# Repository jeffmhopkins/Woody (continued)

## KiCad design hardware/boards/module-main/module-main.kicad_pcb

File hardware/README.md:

# hardware/ — how this directory is organised

*Schematic sheets are generated from the netlists in KiCad 9, and each
physical board has a directory under [`boards/`](boards/) whose netlist is
assembled from the circuits: [`docs/reference/tooling.md`](../docs/reference/tooling.md) §3.*

One circuit per directory. The directory is the unit: the drawing, the parts,
the declared dependencies and the history of what the circuit *used to be* all
sit together, so a change and its record are never in different places.

```
<board>/<circuit>/<circuit>.md     the schematic: ASCII drawing, derivations,
                                   and an ## Interfaces table of every net
                                   that crosses the circuit's boundary
                  bom.csv          this circuit's parts. A FRAGMENT
                  circuit.yaml     declared dependencies. SEEDED, NOT VERIFIED
                  notes.md         past tense only. No live value belongs here
                  sim/             its SPICE simulation: sims.yaml (what is simulated,
                                   and what each run must show), the decks, and
                                   results.yaml, GENERATED by tools/sim.py run and
                                   held to its inputs by check-staleness. A sim/
                                   with a README and no sims.yaml is a contract not
                                   yet run, and says so
                  <circuit>.kicad_sch  THE SOURCE OF TRUTH where it exists
                                   (ADR 0019): connections and part facts.
                                   Edit in KiCad 9
                  netlist.yaml     EXPORTED from the sheet by tools/kicad.py
                                   where one exists - do not edit. Otherwise
                                   hand-written and authoritative until the
                                   circuit is migrated. Every check reads it

boards/<board>/   one KiCad project per physical board: the root sheet
                  places circuit sheets once per instance; board-netlist.yaml
                  is its exported, flattened netlist

nets.yaml                          at hardware/ root: THE MASTER NET LIST,
                                   which owns every net that crosses a circuit
                                   boundary. A netlist.yaml declares only its
                                   own side; this file owns the net
```

> ### The drawing is not the source of truth. Where a `netlist.yaml` exists, that is.
>
> **An ASCII drawing is a picture.** No tool in this repository can read one,
> so nothing checks that a value in a drawing matches the BOM row for the same
> refdes — and on 2026-09-22 a review found four that did not, including
> `R-FB` drawn at a resistance that is not a purchasable E96 value and an
> entry capacitor drawn at half the BOM's value on the rail that matters.
>
> **`tools/check-netlist.py` checks the drawing against the netlist**, and
> the netlist against `bom.csv` and against `nets.yaml`. It runs `--strict`
> from the commit gate, so a page that gains a drawing and no netlist is a
> failure rather than an entry on a list. It resolves a label against EVERY
> netlist, not only the one beside the page, because several pages draw parts
> they do not own.
>
> **Where a drawing and a row disagree and no netlist covers them, `bom.csv`
> wins.** It is generated from fragments, `merge-bom.py --check` proves the
> master matches them, and the commit hook runs it. A drawing has none of
> that behind it.

| Directory | |
|---|---|
| [`carrier/`](carrier/carrier.md) | The instrument's real-time board — 5 circuits |
| [`cluster/`](cluster/cluster-boards.md) | The four key clusters — two key boards and the main board's two thumb clusters — 3 circuits |
| [`module/`](module/module.md) | The 10HP Eurorack module — 12 circuits |
| [`interfaces/`](interfaces/README.md) | The 3 circuits that cross a board boundary |

## The `Interfaces` table

Every circuit page carries one: every net that crosses that circuit's
boundary, one row each. A PCB netlist is transcribed from these, so a row is
a wiring instruction and two pages disagreeing about a net is a short.

**Two drawing shorthands, and they are shorthands — not missing parts.** The
ASCII drawings use a short spelling where the full refdes would break column
alignment. When transcribing a netlist, expand them:

A netlist declares its own alias with `drawn_as:`, which is what makes the
shorthand checkable rather than merely documented; this table is for the
pages that have no netlist yet.

| Drawn as | BOM row |
|---|---|
| `C-TIMER` | `C-TIMER-LOADSW` |
| `C-GATE` | `C-GATE-LOADSW` |

**`J-UMB` is no longer a shorthand.** It was one, for `J-UMBILICAL`, until
ADR 0017 put a real connector of that name on the main board: `J-UMB` is now
its own row, the header that joins the etherCON's adapter to the main board
(ADR 0021), so "`J-UMB` pin N" on an instrument page is that header, and conductor N of
the umbilical as `umbilical-pinmap` numbers them. Both etherCONs carry it on
contact 9 − N (`hardware/interfaces/spi-link/spi-link.md`). On a module page the umbilical
connector is `J-UMBILICAL`, netlisted as `J-UMB-MOD`; the instrument's
etherCON is `J-UMBILICAL-INST`, netlisted as `J-UMB-INST`. Neither is ever
`J-UMB`.

A cold reviewer filed these two, and `J-UMB` when it was a shorthand, as
refdes that "match nothing in `bom.csv`", which was fair — nothing said
otherwise. They are listed here once rather
than expanded in ~40 drawing sites, because widening a label inside a drawing
shifts every column to its right, and that drift is itself a recorded defect
on these pages. One more, an unlabelled `N-FET`, was **not** a shorthand: it
is `Q-LOADSW`, a row created after that drawing was last touched, and it is
now labelled.

| Column | |
|---|---|
| **Node** | The net's name, **qualified** where the same bare name means different things on different boards. `AGND_SENSE`, `AGND_INST` and `AGND_MOD` are three nets; `AGND` alone is a merge waiting to happen. Each row names the drawing's own spelling so a reader can match the two. |
| **Dir** | This circuit's side of the net: `in`, `out`, `in/out`, `ref` (a return or a reference) or `—` (no connection here — the row is context). |
| **Peer** | A bare `board/circuit` id when the other end is a circuit in this tree, a reference designator or part name when it is not, `—` when there is nothing on the other end. |
| **Figure** | A citation into `config/figures.yaml`. The table names nodes; it **does not restate values.** |

**Exactly one page sources a net.** The page holding the part that drives it
says `out` and "Sourced here"; every other page says `in` and names it. Two
pages both claiming to source one net is the defect this column exists to
make visible — it happened to the DAC's `SCLK`/`DIN`/`SYNC`, in two
byte-identical rows.

The two board-crossing tables (`interfaces/breath-sense-link`,
`interfaces/spi-link`) carry an extra **End** column naming which side of the
cable a node sits on, because for those the board is not implied by the page.

*(This definition sat inline in all 23 circuit pages until 2026-09-21 —
twenty-three copies of one paragraph, in a repository whose first rule is
state it once and cite it. It is here, and they cite it.)*

## `circuit.yaml` and its `depends_on` edges

Every circuit directory carries a `circuit.yaml` whose `depends_on` list is
the dependency graph. Four kinds of edge, and **they are not equally
trustworthy** — this section is the one place that says which:

**`circuit:` edges are VERIFIED.** The rule is mechanical, so any edge can be
checked against the two tables it comes from:

> ONE `circuit:` edge per distinct `board/circuit` id in the **Peer** column of
> this circuit's `## Interfaces` table, AND every such edge is declared from
> **both** ends. A peer that is not a circuit in this tree — a connector, the
> Eurorack bus board, a dev board header — is named in the Peer column by its
> reference designator or its name, and creates no edge.

**`adr:`, `fig:` and `refdes:` edges are SEEDED FROM CO-MENTION and are NOT
VERIFIED.** An edge of those three kinds means *"this page mentions this
thing"*, which is a useful starting graph and a bad finished one. Three were
verified false by a cold reviewer, by reading:

| edge | what it really is |
|---|---|
| `pitch-stage` → `R-BIAS-INAMP` | the page names it as an explicit **contrast** |
| `breath-adc` → `C-STRIP-BULK` | a citation of a note about the LED strip |
| `breath-receive` → `U-OPA-PITCH` | a package-count consequence, not a use |

All three are still declared. **Expect more of that shape.**

**Direction is not recorded.** Several pairs are mutual, which is honest for a
net shared between two circuits and useless for ordering anything.

**What IS guaranteed for every edge, verified or seeded: it RESOLVES.** A
`refdes:` names a BOM row that exists, a `fig:` names a register entry, a
`circuit:` names a declared id. That is what catches a dependency on a deleted
part — the semantic half `CLAUDE.md` §5 says a grep cannot reach.

*(This sat as a 39-line comment header inside all 23 `circuit.yaml` files —
byte-identical, twenty-three copies — until 2026-09-22. Same defect as the
`## Interfaces` definition above, found the same way, fixed the same way.)*

## Two rules that will bite you

**`bom.csv` here is GENERATED.** `tools/merge-bom.py` rebuilds it from the
per-circuit fragments, so **a direct edit survives until the next run of that
tool and then disappears without a word.** Edit the fragment. A row lives with
the circuit **whose page derives its value** — not where it is mentioned, not
where it is mounted. `merge-bom.py --check` proves the master still matches
and `check-staleness.py` reports it as a FAIL, loudly rather than silently —
but the hook only reports; nothing blocks the commit (`CLAUDE.md`, rule 2).

**Numbers shared between documents are not written here.** They live in
`config/figures.yaml`, stated once by their owner and **cited by name**
everywhere else. This whole repository is organised around one recorded
failure — a value changes and the documents derived from it do not follow —
and citation is the only form that cannot go stale. `CLAUDE.md` has the rule
and the three-step procedure for changing a tracked figure.

## What is deliberately not here

`hardware/unplaced.csv` holds the BOM rows **no schematic page derives**.
That is a count, not a dumping ground: a part nobody has drawn.

It has shrunk twice; `wc -l hardware/unplaced.csv` is the count, and a
number written here goes stale the next time a row is placed. Sixteen rows
were drawn all along — the
DAC, the in-amp, the LM317 and its divider, the entry diodes, the four
beads, the bulk capacitors, both load-switch capacitors, the module's level
shifter and the LT5400 — and were sitting in the undrawn pile because
assignment matched on **reference designator** while those parts are drawn
under a local label (`R1`, `C_cm`, `FB2`, `R_G`) or a part number
(`INA828`, `LM317LZ`, `DAC8568`). A count of undrawn parts that includes
every principal IC on a board is not a count of anything.

What remains is genuinely unplaced, and most of it is mechanical — the oak,
the acrylic, the adhesives, the fasteners — plus the parts whose circuit has
no page yet.

Drawings that span more than one circuit were **left whole** rather than
redrawn, and the circuits cite them. `carrier.md`'s §2 figure carries three
circuits in one connected picture; dividing it would mean redrawing it, and a
redraw is not a move.

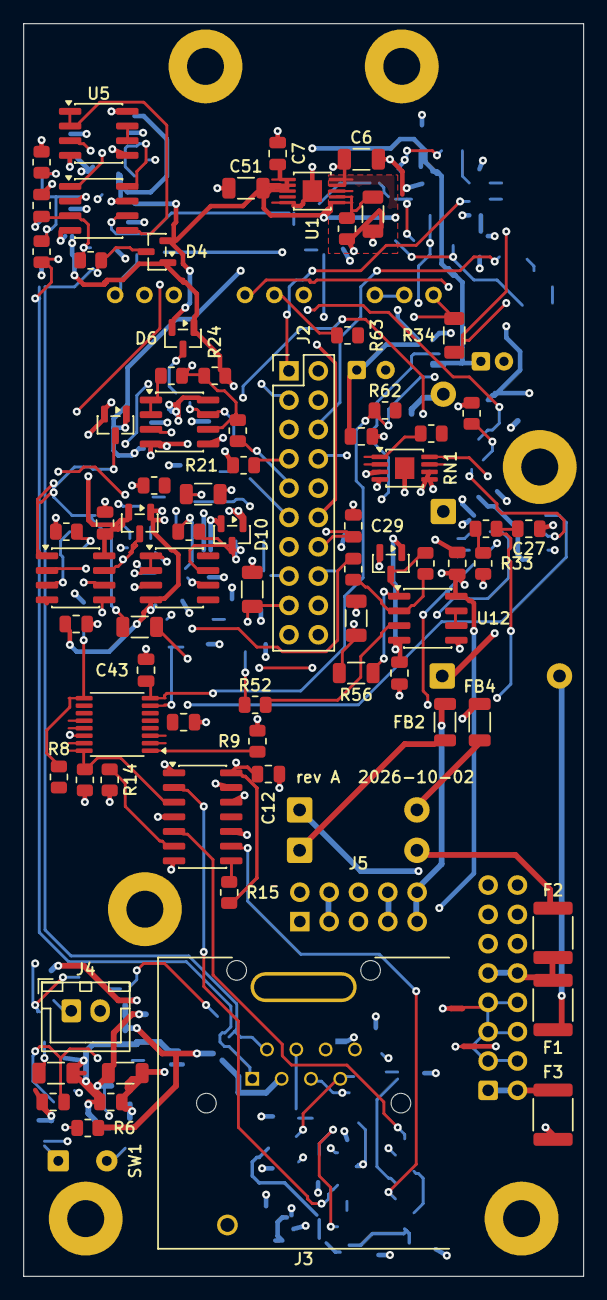
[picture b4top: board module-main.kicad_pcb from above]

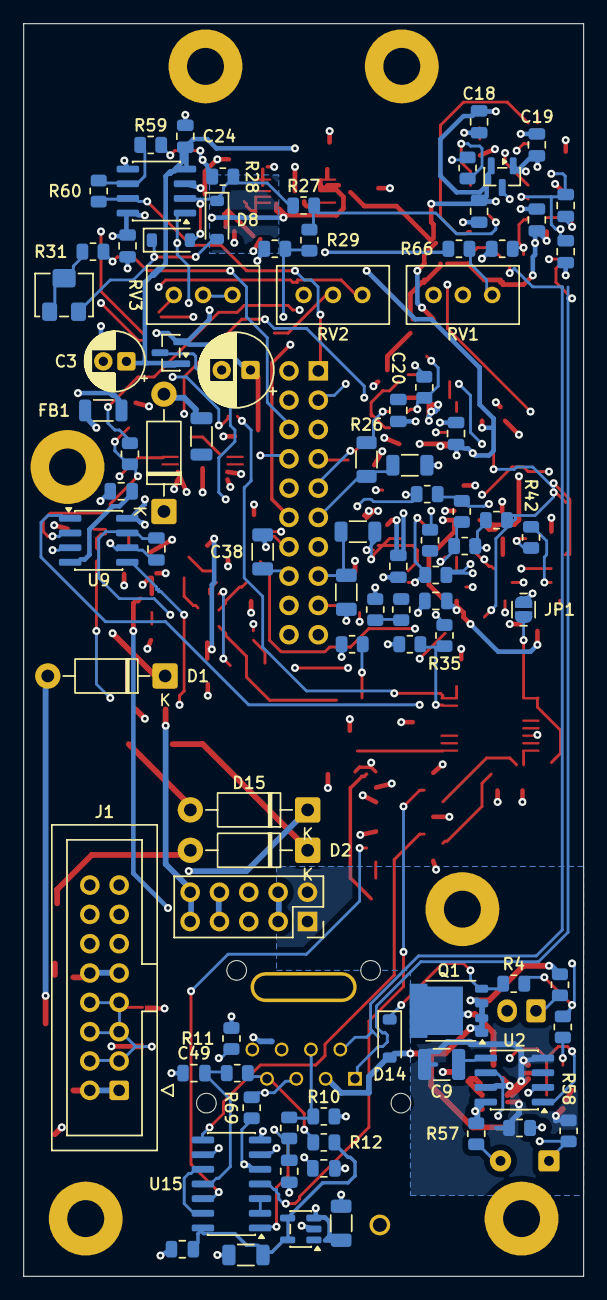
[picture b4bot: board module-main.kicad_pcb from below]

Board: 4 copper layers, 48.5 x 108.5 mm, 173 parts (88 on the bottom side), 110 nets.

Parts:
C1: 100uF; CP_Radial_D6.3mm_P2.50mm
C3: 47uF; CP_Radial_D5.0mm_P2.00mm
C5: 100nF; C_1206_3216Metric
C6, C51: 10uF; C_1206_3216Metric
C7, C10, C11, C12, C16, C17, C18, C19, C20, C21, C23, C24, C25, C26, C30, C31, C32, C33, C34, C35, C40, C43, C50: 100nF; C_0805_2012Metric
C8, C36, C37, C38, C39: 82nF; C_1206_3216Metric
C9: 10uF; C_1210_3225Metric
C13, C14: 1.5nF; C_0805_2012Metric
C15: 15nF; C_0805_2012Metric
C22: 330nF film; C_1206_3216Metric
C27, C29: 10nF; C_0805_2012Metric
C28: 2.2nF; C_0805_2012Metric
C41, C42: 4.7uF; C_1206_3216Metric
C47, C48, C49: 47pF C0G; C_0805_2012Metric
D1, D2, D3, D15: 1N5817; D_DO-41_SOD81_P10.16mm_Horizontal
D4, D5, D6, D9, D10, D11, D12, D13: BAV99; SOT-23
D7, D8: 1N4448W; D_SOD-123
D14: 15V; D_SOD-123
F1, F3: MF-MSMF020/60-2; Fuse_1812_4532Metric
F2: MF-MSMF075/33X-2; Fuse_1812_4532Metric
FB1, FB2, FB3, FB4: 600R @ 100MHz; L_1206_3216Metric
H1: MECH-STANDOFF-MOD 1; MountingHole_3.2mm_M3_Pad
H2: MECH-STANDOFF-MOD 2; MountingHole_3.2mm_M3_Pad
H3: MECH-PANEL-STANDOFF-MOD 1; MountingHole_3.2mm_M3_Pad
H4: MECH-PANEL-STANDOFF-MOD 2; MountingHole_3.2mm_M3_Pad
H5: MECH-STANDOFF-ISO 1; MountingHole_3.2mm_M3_Pad
H6: MECH-STANDOFF-ISO 2; MountingHole_3.2mm_M3_Pad
J1: 2x8 2.54mm shrouded box header (16-pin); IDC-Header_2x08_P2.54mm_Vertical
J2: 2x10 2.54mm pin header; PinHeader_2x10_P2.54mm_Vertical
J3: Neutrik NE8FAV; Neutrik_NE8FAV_etherCON_Vertical
J4: JST B2B-XH-A; JST_XH_B2B-XH-A_1x02_P2.50mm_Vertical
J5: 2x5 2.54mm pin header; PinHeader_2x05_P2.54mm_Vertical
JP1: 2-pad solder link; SolderJumper-2_P1.3mm_Open_RoundedPad1.0x1.5mm
NT1, NT2, NT3: net tie; NetTie-2_SMD_Pad0.5mm
Q1: PSMN2R0-30YLE; LFPAK56
R1: 52.3k 0.1%; R_0805_2012Metric
R3: 50m 1% 1W; R_1206_3216Metric
R4: 10R 5%; R_0805_2012Metric
R5: 1k 5%; R_0805_2012Metric
R6: 35.7k 1%; R_0805_2012Metric
R7: 5.11k 1%; R_0805_2012Metric
R8, R10, R11, R13, R14, R15, R22, R28, R29, R30, R58, R59: 10k 1%; R_0805_2012Metric
R9: 0R strap; R_0805_2012Metric
R12, R33, R36, R38, R43, R48, R53: 100k 1%; R_0805_2012Metric
R16, R17, R39, R44, R49, R54, R65: 10k 0.1%; R_0805_2012Metric
R18, R19: 1M 1%; R_0805_2012Metric
R20: 42.2k 0.1%; R_0805_2012Metric
R21: 7.15k 1%; R_0805_2012Metric
R23: 21.0k 1%; R_0805_2012Metric
R24: 95.3k 1%; R_0805_2012Metric
R25: 40.2k 1%; R_0805_2012Metric
R26, R34, R41, R46, R51, R56: 1k 1%, >=500mW; R_1206_3216Metric
R27, R60: 20k 1%; R_0805_2012Metric
R31: 2.7k 1%; R_0805_2012Metric
R32, R35, R37, R42, R47, R52, R68, R69, R70: 1k 1%; R_0805_2012Metric
R40, R45, R50, R55: 30k 0.1%; R_0805_2012Metric
R57: 68k 1%; R_0805_2012Metric
R61: 100R 0.1%; R_0805_2012Metric
R62: 1k 0.1%; R_0805_2012Metric
R63: 22.1k 0.1%; R_0805_2012Metric
R64: 200R 0.1%; R_0805_2012Metric
R66: 42.2k 1%; R_0805_2012Metric
R71: 2k2 1%; R_0805_2012Metric
RN1: 10k; MSOP-8-1EP_3x3mm_P0.65mm_EP1.68x1.88mm
RV1, RV2: 10k multiturn cermet; Potentiometer_Bourns_3296W_Vertical
RV3: 200R multiturn cermet; Potentiometer_Bourns_3296W_Vertical
RV4: 10k 10% sealed SMD cermet; Potentiometer_Bourns_3224W_Vertical
SW1: NKK M2011SD4G01; SolderWire-0.25sqmm_1x02_P4.2mm_D0.65mm_OD1.7mm
U1: LT3042EMSE; MSOP-10-1EP_3x3mm_P0.5mm_EP1.68x1.88mm
U2: LT1641-1IS8; SOIC-8_3.9x4.9mm_P1.27mm
U3: DAC8568ICPW; TSSOP-16_4.4x5mm_P0.65mm
U4: 74AHCT125; SOIC-14_3.9x8.7mm_P1.27mm
U5, U7, U9, U10, U11, U12: OPA2197; SOIC-8_3.9x4.9mm_P1.27mm
U6: INA828IDR; SOIC-8_3.9x4.9mm_P1.27mm
U8: OPA2197IDR; SOIC-8_3.9x4.9mm_P1.27mm
U13: ADP7118AUJZ-5.0; TSOT-23-5
U15: 74AHCT14; SOIC-14_3.9x8.7mm_P1.27mm

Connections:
/AGND_SENSE: D4.3, J3.2, R16.1
/BREATH_INAMP_OUT: R27.1, R29.1, U6.6
/BREATH_JACK: C22.1, J2.11, R26.2
/BREATH_SENSE: D5.3, J3.1, R17.1
/BREATH_SHAPED: J2.1, R60.2, U8.7
/CS_MOD: J3.7, R12.1, R70.1
/DAC_AVDD: C6.1, C11.1, C12.1, J2.12, R8.1, R15.2, R66.1, U1.9, U1.10, U3.3, U4.14
/DAC_CH1: R32.1, R33.1, U3.4
/DAC_CH2: R37.1, R38.1, U3.13
/DAC_CH3: R42.1, R43.1, U3.5
/DAC_CH4: R47.1, R48.1, U3.12
/DAC_CH5: R52.1, R53.1, U3.6
/DAC_CH7: R35.1, R36.1, U3.7
/DIN: R14.1, U3.15, U4.6
/GAIN_FLOOR: J2.7, R21.1
/GAIN_WIPER: J2.3, U7.3
/ISO_FB2: FB2.2, J5.9, J5.10
/ISO_FILT_NEG: FB4.2, J5.7, J5.8
/MOD1_JACK: C36.1, J2.15, R41.2
/MOD2_JACK: C37.1, J2.17, R46.2
/MOD3_JACK: C38.1, J2.16, R51.2
/MOD4_JACK: C39.1, J2.20, R56.2
/MOSI: J3.5, R11.1, R69.1
/OFFSET_WIPER: J2.9, R23.1
/PITCH_JACK: C29.1, J2.14, R34.2, RV3.1
/RESP_V_IN_HALF: J2.4, R29.2, R30.1
/RESP_V_SHAPED: J2.8, R28.2, R59.1, U8.1
/RESP_WIPER: J2.6, R31.1
/SCLK: J3.4, R10.1, R68.1
/SCLK_DAC: R13.1, U3.16, U4.3
/SYNC: R15.1, U3.2, U4.8
/UMBILICAL_POS12: D14.2, J3.3, Q1.1, Q1.2, Q1.3, R6.1, R71.1
/VREFOUT: C43.1, R62.1, RV2.3, U3.8
/breath-output-stage/BREATH_OUT: D6.3, R25.2, R26.1, U7.7
/breath-output-stage/BUF_OUT: R22.1, U7.1, U7.2
/breath-output-stage/SUM_NODE: R22.2, R23.2, R24.2, R25.1, U7.6
/breath-receive-stage/GAIN_SET: R20.1, U6.1
/breath-receive-stage/GAIN_SET_B: R20.2, U6.8
/breath-receive-stage/IN_NEG: C14.1, C15.2, R17.2, R19.1, U6.2
/breath-receive-stage/IN_POS: C13.1, C15.1, R16.2, R18.1, U6.3
/breath-receive-stage/REF_DRIVE: U5.1, U5.2, U6.5
/breath-receive-stage/SPARE_B_OUT: U5.6, U5.7
/breath-receive-stage/TRIM_WIPER: RV1.2, U5.3
/breath-receive-stage/ZERO_TOP: R66.2, RV1.3
/breath-response-shaper/DIODE_BRANCH: D7.1, D8.2, RV4.3
/breath-response-shaper/RESP_TRIM: R31.2, RV4.1, RV4.2
/breath-response-shaper/RESTORE_SUM: R59.2, R60.1, U8.6
/breath-response-shaper/VIRTUAL_GND: D7.2, D8.1, R27.2, R28.1, U8.2
/dac8568/CLR: JP1.1, R8.2, U3.9
/dac8568/LDAC: R9.1, U3.1
/digital-and-supervision/CS_BUF: U4.9, U15.12
/digital-and-supervision/CS_N: U15.10, U15.13
/digital-and-supervision/CS_RC: C49.1, R70.2, U15.11
/digital-and-supervision/MOSI_BUF: U4.5, U15.8
/digital-and-supervision/MOSI_N: U15.6, U15.9
/digital-and-supervision/MOSI_RC: C48.1, R69.2, U15.5
/digital-and-supervision/SCLK_BUF: U4.2, U15.4
/digital-and-supervision/SCLK_N: U15.2, U15.3
/digital-and-supervision/SCLK_RC: C47.1, R68.2, U15.1
/mod-channels/MINUS_1: R39.2, R40.1, U10.6
/mod-channels/MINUS_2: R44.2, R45.1, U11.2
/mod-channels/MINUS_3: R49.2, R50.1, U11.6
/mod-channels/MINUS_4: R54.2, R55.1, U12.2
/mod-channels/OUT_1: D10.3, R40.2, R41.1, U10.7
/mod-channels/OUT_2: D11.3, R45.2, R46.1, U11.1
/mod-channels/OUT_3: D12.3, R50.2, R51.1, U11.7
/mod-channels/OUT_4: D13.3, R55.2, R56.1, U12.1
/mod-channels/PLUS_1: R37.2, U10.5
/mod-channels/PLUS_2: R42.2, U11.3
/mod-channels/PLUS_3: R47.2, U11.5
/mod-channels/PLUS_4: R52.2, U12.3
/mod-channels/REF_PLUS: R35.2, U10.3
/mod-channels/SPARE_C_OUT: U12.6, U12.7
/mod-channels/VREF_MOD: R39.1, R44.1, R49.1, R54.1, U10.1, U10.2
/panel-led/LED_ANODE: J4.1, R71.2
/pitch-stage/AMP_OUT: C28.1, D9.3, R34.1, U9.7
/pitch-stage/GAIN_TRIM_MID: RN1.7, RV3.2, RV3.3
/pitch-stage/MINUS_NODE: C28.2, RN1.2, RN1.8, U9.6
/pitch-stage/PLUS_NODE: C27.1, R32.2, U9.5
/pitch-stage/R1_BOTTOM: R61.1, RN1.1
/pitch-stage/TRIM_WIPER: R63.1, RV2.2
/pitch-stage/VREF_BUFFERED: R61.2, R64.1, U9.1
/pitch-stage/VREF_FB: R64.2, R65.1, U9.2
/pitch-stage/VREF_SUM: R62.2, R63.2, U9.3
/power-entry/BUS_GND: J1.3, J1.4, J1.5, J1.6, J1.7, J1.8, NT1.2, NT2.2
/power-entry/BUS_NEG12_RAW: D15.1, F3.1, J1.1, J1.2
/power-entry/BUS_POS12_RAW: F1.1, F2.1, J1.9, J1.10
/power-entry/DAC_REG_SET: C5.1, R1.1, U1.7
/power-entry/NEG12_D4: D15.2, FB4.1
/power-entry/NEG12_FB: D3.2, FB3.1
/power-entry/NEG12_PTC3: D3.1, F3.2
/power-entry/POS12_D1: D1.1, FB1.1
/power-entry/POS12_D2: D2.1, FB2.1
/power-entry/POS12_PTC1: D1.2, F1.2
/power-entry/POS12_PTC2: D2.2, F2.2
/umbilical-load-switch/FB: R6.2, R7.1, U2.2
/umbilical-load-switch/GATE_COMP_MID: C8.1, R5.2
/umbilical-load-switch/GATE_DRIVE: R4.1, R5.1, U2.6
/umbilical-load-switch/GATE_NODE: D14.1, Q1.4, R4.2
/umbilical-load-switch/ON: C40.1, R58.1, SW1.1, U2.1
/umbilical-load-switch/ON_SW: R57.2, SW1.2
/umbilical-load-switch/SENSE_NODE: Q1.5, R3.2, U2.7
/umbilical-load-switch/TIMER: C9.1, U2.5
AGND_MOD: C1.2, C3.2, C5.2, C6.2, C7.2, C11.2, C13.2, C14.2, C16.2, C17.2, C18.2, C19.2, C20.2, C21.2, C22.2, C23.2, C24.2, C25.2, C26.2, C27.2, C29.2, C30.2, C31.2, C32.2, C33.2, C34.2, C35.2, C36.2, C37.2, C38.2, C39.2, C43.2, C51.2, J2.2, J2.5, J2.10, J2.13, J2.18, J4.2, JP1.2, NT1.1, R1.2, R9.2, R18.2, R19.2, R21.2, R30.2, R33.2, R36.2, R38.2, R43.2, R48.2, R53.2, R65.2, RN1.3, RN1.4, RN1.5, RN1.6, RN1.9, RV1.1, RV2.1, U1.5, U1.8, U1.11, U3.14, U5.5, U7.5, U8.3, U8.5, U12.5
DIG_GND: C12.2, C41.2, C42.2, C47.2, C48.2, C49.2, C50.2, J3.8, NT2.1, NT3.2, R10.2, R11.2, R13.2, R14.2, U4.1, U4.4, U4.7, U4.10, U4.12, U4.13, U13.2, U15.7
ISO_POS12: C10.1, J5.3, J5.4, R3.1, R57.1, U2.8
LOGIC_5V: C42.1, C50.1, R12.2, U13.4, U13.5, U15.14
MODULE_ANALOG_NEG12: C3.1, C17.1, C19.1, C21.1, C24.1, C26.1, C31.1, C33.1, C35.1, D4.1, D5.1, D6.1, D9.1, D10.1, D11.1, D12.1, D13.1, FB3.2, R24.1, U5.4, U6.4, U7.4, U8.4, U9.4, U10.4, U11.4, U12.4
MODULE_ANALOG_POS12: C1.1, C7.1, C16.1, C18.1, C20.1, C23.1, C25.1, C30.1, C32.1, C34.1, C41.1, C51.1, D4.2, D5.2, D6.2, D9.2, D10.2, D11.2, D12.2, D13.2, FB1.2, U1.1, U1.2, U1.3, U1.6, U5.8, U6.7, U7.8, U8.8, U9.8, U10.8, U11.8, U12.8, U13.1, U13.3
PWR_GND: C8.2, C9.2, C10.2, C40.2, J3.6, J5.1, J5.2, NT3.1, R7.2, R58.2, U2.4

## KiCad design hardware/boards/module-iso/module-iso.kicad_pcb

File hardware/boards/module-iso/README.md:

# Module iso board — `module-iso`

The Eurorack module's third board (ADR 0023 point 2, amended 2026-10-03 by the
owner: *"3 boards for module is correct"*; issue #22): **the instrument's
isolated supply** — `U-ISO` (RECOM RPA20-2412SAW, ADR 0027) and its filter
(`L-ISO-IN`, `L-CM-ISO`, `C-ISO-BULK` `C2`, `C-ISO-IN`, `C-ISO-Y`,
`C-ISO-OUT`) — on a board of its own, parallel to
[`module-main`](../module-main/README.md) and **behind it**.

**Why a board of its own.** On the main board's rear face `U-ISO`'s 25 mm body
put its pins, its 2 mm isolation gap and its `PWR_GND` return pour in the
middle of the DAC's corner, where the DAC meets the mod channels. Twenty
connections stayed unrouted there, and re-placing the corner first left more,
not fewer (`module-main/README.md`). Off the main board, the converter takes
none of its copper.

**Its outline is derived** in the module CAD (`config/module.yaml`
`iso_board`; `mechanical/module/export/iso-board.dxf`): the boards' side edges,
a bottom edge just above the NE8FAV's tails, a notch at its lower right that
`J-PWR-EURO` and its mated socket stand in, and a top edge (`iso_board.y1`)
below the rear trimmers, so each stays adjustable from behind
(`mechanical/module/drc.echo`, *trimmers adjustable from behind*). It stands
off the main board's rear face on two stock spacers used uncut, at opposite corners,
(`MECH-STANDOFF-ISO`): **the gap is the spacer** (*iso board gap*). Its parts
stand on its **rear** face, away from the main board; on the front only
`U-ISO`'s tails and `J-B2B-ISO`'s posts stand in the gap, over main-board
parts no taller than `iso_board.under_h`.

> **Status: laid out and routed by `tools/pcb.py` (`kind: module`), 2026-10-03.**
> Two layers, **a power layout drawn by hand** (2026-10-03, the owner's review of
> the first, autorouted one; *The layout*). `pcb.py check` passes: KiCad's DRC with schematic parity, nothing
> unrouted, every courtyard inside the board, every CAD-placed part where
> `pcb-geometry.echo` puts it, the isolation gap, and `J-B2B-ISO` mating with
> the main board's pin for pin (`check_b2b`). The mask colour is **not
> decided** — green until the owner says (*Open*).

## J-B2B-ISO — the allocation

A 2 × 5 header (`J-B2B-ISO`, Samtec TSW-105-09-G-D) soldered through this
board and the main board: **pin *k* is one conductor on both**, so both
sheets net it the same (`tools/kicad.py check`) and both layouts put it on the
**top face, unmirrored**, pin 1 at the bottom left seen from the panel
(`pcb-geometry.echo`). Its insulator is on the main board's rear face; this
board has only its posts. Each net on two pins, for the converter's current:

| Pins | Net | Side of the barrier |
|---|---|---|
| 1, 2 | `PWR_GND` | output: `U-ISO`'s return, to the load switch and `NT-UMB-MOD` on the main board |
| 3, 4 | `ISO_POS12` | output: the isolated +12 V, to the load switch |
| 5, 6 | — (open) | **the isolation gap**: two pitches between the sides |
| 7, 8 | `ISO_FILT_NEG` | input: the −12 V leg after `FB4` |
| 9, 10 | `ISO_FB2` | input: the +12 V leg after `PTC-ISO`, `D2` and `FB2` |

The output pairs are at the left end, under `U-ISO`'s output row; the input
pairs at the right, toward `L-ISO-IN` and `L-CM-ISO`.

## The layout

`layout.yaml` beside this file records how the first layout was made; the
`.kicad_pcb` is the source now. `U-ISO` and `J-B2B-ISO` are placed by the
module CAD, `U-ISO` turned so its output row (pins 4, 5, 6) runs along the
bottom beside the header and its input pins (1, 2) are at the top.

**It is a power layout, placed and drawn by hand** — the first layout's
autorouted, one-direction-per-layer tracks were the owner's objection
(2026-10-03: *"the strict vertical/horizontal routing is completely
unnecessary"*). The parts follow the current: `J-B2B-ISO`'s input pairs →
`L-ISO-IN` (`L1`) straight above them → `L-CM-ISO` (`L2`, its IN pads down,
OUT pads up) → `C-ISO-BULK` (`C2`) and `U-ISO`'s input pins at the top, with
`C-ISO-IN` (`C44`) on the front between those pins; then `U-ISO`'s output row →
`C-ISO-OUT` (`C45`) → `J-B2B-ISO`'s output pairs. `C-ISO-Y` (`C46`) is on the
front across the barrier beside the 0V pin. `C44` and `C46` are the only
front-face parts.

- **Three pour regions, each on both faces and stitched**: `PWR_GND` under the
  output side (the rear pour stops short of `U-ISO`'s body), `ISO_VIN_NEG`
  over the converter's input side, `ISO_FILT_NEG` under the filter's input.
  They are the returns; no return is a track.
- **The supply nets are straight runs with 45° bends**, 1.2–1.5 mm wide:
  `ISO_POS12` from +Vout through `C45`'s + pad to pair 3-4; `ISO_VIN_POS` from
  `L2`'s OUT_POS over the top to `C2`'s + pad and down to +Vin (and on the front
  through `C44` to `C46`); `ISO_FB2` and `ISO_FILT_POS` from the header through
  `L1` to `L2`. One via per stitch, none in a supply run.
- **The isolation gap** (`layout.yaml` `isolation:`, 2.0 mm, functional, not
  a safety rating): the output region's pours stop 2 mm or more short of the
  input regions' on both faces, across `U-ISO`'s middle and down past the
  header's open pair 5-6; `C46` bridges it by design.
- The two standoff pads on no net (`power-entry.md`, *Grounding*).

## Files

| File | What it is |
|---|---|
| `module-iso.kicad_sch` (+ power-entry's `iso` page) | **Source** (ADR 0019) |
| `board-netlist.yaml` | Exported (`python3 tools/kicad.py export hardware/boards/module-iso`), with KiCad's ERC |
| `*.sch.png` | Renders, recorded in `hardware/SHEETS.csv` |
| `module-iso.kicad_pcb`, `module-iso.kicad_pro` | **Source** since the first layout: edit in KiCad 9; `python3 tools/pcb.py check hardware/boards/module-iso` holds it |
| `layout.yaml` | How the first layout was made |
| `module-iso.pcb-*.png`, `fab/` | Written by `python3 tools/pcb.py render`, recorded in `hardware/SHEETS.csv` |
| `fp-lib-table`, `sym-lib-table` | Register `hardware/lib/` (`U-ISO`'s and `L-CM-ISO`'s footprints) |

## Open, and what decides each

| Item | Decided by |
|---|---|
| The boards' mask colour (green in `layout.yaml` `fab:` until decided) | The owner, before the first order |
| `J-B2B-ISO`'s LCSC part number (the MPN is the TSW family's, as `J-B2B-MOD`) | The module's parts order |
| The spacers' material: `MECH-STANDOFF-ISO` is the same 8 mm metal stock as `MECH-STANDOFF-MOD`, whose metal part is not chosen yet (its row) | The module CAD owner, with `MECH-STANDOFF-MOD` |

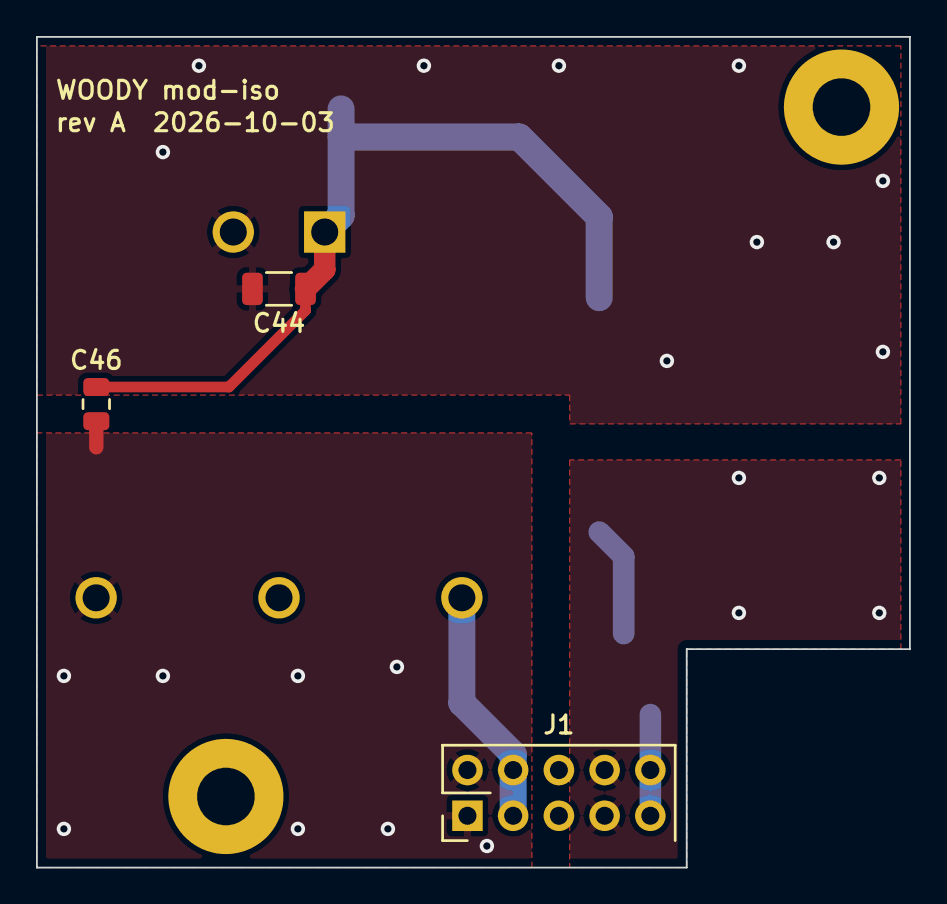
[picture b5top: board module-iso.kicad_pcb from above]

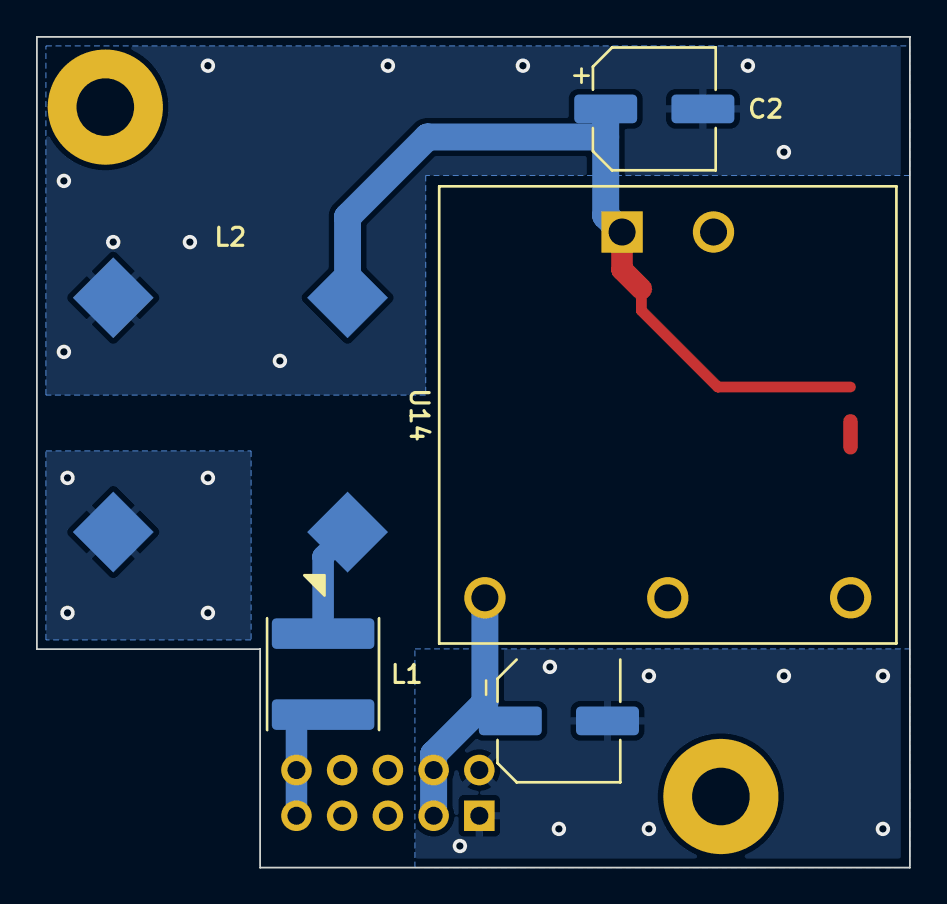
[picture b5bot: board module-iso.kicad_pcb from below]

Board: 2 copper layers, 48.5 x 46.2 mm, 10 parts (5 on the bottom side), 7 nets.

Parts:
C2: 100uF 50V; CP_Elec_6.3x7.7
C44: 4.7uF 50V; C_1206_3216Metric
C45: 100uF 25V; CP_Elec_6.3x5.8
C46: 22nF; C_0805_2012Metric
H1: MECH-STANDOFF-ISO 1; MountingHole_3.2mm_M3_Pad
H2: MECH-STANDOFF-ISO 2; MountingHole_3.2mm_M3_Pad
J1: 2x5 2.54mm pin header; PinHeader_2x05_P2.54mm_Vertical
L1: 22uH; L_Sunlord_SWPA6028S
L2: 1mH; L_CommonModeChoke_Bourns_PM3700
U14: RPA20-2412SAW; Converter_DCDC_RECOM_RPA20-RP20-xxxxSAW_THT

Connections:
/ISO_FB2: J1.9, J1.10, L1.1
/ISO_FILT_NEG: J1.7, J1.8, L2.4
/ISO_POS12: C45.1, J1.3, J1.4, U14.6
/PWR_GND: C45.2, C46.2, J1.1, J1.2, U14.4
/power-entry/ISO_FILT_POS: L1.2, L2.1
/power-entry/ISO_VIN_NEG: C2.2, C44.2, L2.3, U14.2
/power-entry/ISO_VIN_POS: C2.1, C44.1, C46.1, L2.2, U14.1

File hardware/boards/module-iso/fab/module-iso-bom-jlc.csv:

Comment,Designator,Footprint,JLCPCB Part #
100uF 25V,C45,CP_Elec_6.3x5.8,C729678
1mH,L2,L_CommonModeChoke_Bourns_PM3700,C2662215
22nF,C46,C_0805_2012Metric,C77069
22uH,L1,L_Sunlord_SWPA6028S,C51349
4.7uF 50V,C44,C_1206_3216Metric,C132170

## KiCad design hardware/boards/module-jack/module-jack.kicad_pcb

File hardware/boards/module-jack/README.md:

# Module jack board — `module-jack`

The Eurorack module's front board (ADR 0023), behind the panel where the
jacks' bodies put it: the six jacks and the three pots, and nothing else.

**Its outline is a plain rectangle** (ADR 0024 point 15, the owner,
2026-10-01): full width, from just below the bottom jack row's footprints
(`config/module.yaml` `boards.jack_y0`, derived there) to the top edge it
shares with the main board — `mechanical/module/export/jack-board.dxf`. The
toggle's row and the etherCON are below it, so nothing passes through it;
until 2026-10-01 it was a U whose legs reached down beside them.
Everything it connects to is on [`module-main`](../module-main/README.md),
through `J-B2B-MOD`.

> **Status: laid out and routed by `tools/pcb.py` (`kind: module`), 2026-10-02.**
> `pcb.py check` passes: KiCad's DRC with schematic parity is clean, nothing is
> unrouted, every courtyard is inside the board, every CAD-placed part is
> where `mechanical/module/export/pcb-geometry.echo` puts it, and `J-B2B-MOD`
> mates with the main board's pin for pin. Two layers, `AGND_MOD` poured on
> both; layer 1 runs vertically and layer 2 across (`layout.yaml`
> `directions:`). The mask colour is **not decided** — green until the owner
> says (*Open*). The sheets are the source and pass KiCad's ERC. Every part
> has a footprint; the parts still missing a bought part are under *Open*.

## The layout

`layout.yaml` beside this file records how the first layout was made; the
`.kicad_pcb` is the source now. Everything but one part is placed by the
module CAD: the six jacks by their pins along the CAD's pin line, the pots by
their pins, `J-B2B-MOD` on the top face unmirrored, `H1`/`H2` on the CAD's
standoffs. What the layout decided:

- **`D-ESD-PITCH` (`D2`) on the rear, between `J-CV-PITCH`'s tip and its
  switch pad** — pitch-stage.md's *at the jack's tip and sleeve pads, before
  the trace leaves*.
- **`J-B2B-MOD`'s courtyard is drawn on the rear** (`connectors:` `body:
  rear`): its insulator is on the main board's side, so on the front only its
  pins stand between the jacks. On the front it overlapped every jack's
  courtyard.
- **The R0904N's courtyard** (`hardware/lib/woody.pretty`) was its bounding
  box, which reached the standoffs' heads between the pots; it now follows
  the body and the snap-in slots' pads, each 0.25 round.
- The CAD's jack positions put the bottom row's courtyards 0.055 mm inside
  the board's bottom edge (`config/module.yaml` `boards.jack_y0`'s
  derivation), and the outer pots' snap-in lugs 0.4 mm inside the sides.

It places:
- the `jack` pages of [`pitch-stage`](../../module/pitch-stage/pitch-stage.md)
  (`J-CV-PITCH`), [`breath-output-stage`](../../module/breath-output-stage/breath-output-stage.md)
  (`J-CV-BREATH`, `POT-GAIN`, `POT-OFFSET`),
  [`breath-response-shaper`](../../module/breath-response-shaper/breath-response-shaper.md)
  (`POT-RESP`) and [`mod-channels`](../../module/mod-channels/mod-channels.md)
  (`J-CV-MOD1`…`4`);
- **`J-B2B-MOD`** on its root sheet: the same header as the main board's, pin
  for pin. The allocation and its reasoning are in
  [`module-main/README.md`](../module-main/README.md#j-b2b-mod--the-allocation);
  `tools/kicad.py check` fails if the two sheets net a pin differently. This
  instance is `Assembly = none`: the one header is bought once.
  **Lay it out on the TOP side (F.Cu), NOT mirrored**, although its body is
  on this board's rear (the insulator is on the main board's front face).
  Pin *k* is one straight conductor through both boards, so it sits at the
  same panel-frame place on both, and both boards' KiCad top views are the
  panel view (`config/module.yaml` frame note): this board takes the same
  unmirrored pin map as the main board, pin 1 at the top left
  (`mechanical/module/export/pcb-geometry.echo` `J-B2B-MOD`). Put on B.Cu,
  the natural side for a part whose body is on the rear, it mirrors: odd and
  even columns swap and every net lands one column over. `tools/pcb.py
  check` catches that since 2026-10-02 (`pcb_module.check_b2b`): the header
  must be on the top face, and each pin k at the same panel-frame place and
  on the same net as the main board's.

The parts carry the references KiCad gives them on this board (`J1`, `RV2`);
`board-netlist.yaml` gives each one's BOM row (`of`) and circuit (`sheet`).
The same header is `J7` here and `J2` on the main board.

## Files

| File | What it is |
|---|---|
| `module-jack.kicad_sch` (+ the pages it places) | **Source** (ADR 0019) |
| `board-netlist.yaml` | Exported (`python3 tools/kicad.py export hardware/boards/module-jack`), with KiCad's ERC |
| `*.sch.png` | Renders, recorded in `hardware/SHEETS.csv` |
| `module-jack.kicad_pcb`, `module-jack.kicad_pro` | **Source** since the first layout (`python3 tools/pcb.py layout`, then `route`): edit in KiCad 9; `python3 tools/pcb.py check hardware/boards/module-jack` holds it |
| `layout.yaml` | How the first layout was made: the parts' places, the rules, planes and checks' inputs |
| `module-jack.pcb-*.png`, `fab/` | Written by `python3 tools/pcb.py render`, recorded in `hardware/SHEETS.csv` |
| `fp-lib-table`, `sym-lib-table` | Register `hardware/lib/` (the R0904N pot footprint) |

**The standoff pads are on the sheet:** `H1` and `H2` (`MountingHole_3.2mm_M3_Pad`, Row `MECH-STANDOFF-MOD`, excluded from the BOM) on `AGND_MOD` — the two standoffs above the pots (`standoff.at`), which with the six jack nuts are all that hold this board. It has no low standoffs: the main board's two low mounting points go to the panel (`MECH-PANEL-STANDOFF-MOD`, ADR 0024 point 15). The main board's pads are on no net, so they need no symbol and are placed board-only by the layout.

**The power LED is not on this board** since 2026-10-01: `LED-PANEL` is a panel-mount indicator whose lead plugs into `J-LED-PANEL` on the main board's front face (ADR 0024 points 15 and 16), and `J-B2B-MOD` pin 19, which carried its supply, is spare and unconnected here.

## Decided 2026-09-30

- **Two layers, 1.6 mm.** This board's only ground is `AGND_MOD`, arriving on
  `J-B2B-MOD`'s five ground pins (`dig-gnd-topology`).
- **The metal standoffs' pads are `AGND_MOD` here** and on no net on the main
  board, so they add no second tie between the boards.

## Open, and what decides each

| Item | Decided by |
|---|---|
| The pots and jacks have no LCSC number (Thonk and Song Huei/Alpha, bought by hand) | Nothing to decide: hand-placed, bought from the maker's stockists. `POT-GAIN`/`POT-OFFSET` are Song Huei R0904N with the 18-tooth **KC** shaft the T18 knob needs, `POT-RESP` Alpha's centre-click RV09 (rows) |
| The boards' mask colour (green in `layout.yaml` `fab:` until decided) | The owner, before the first order |
| The pots' shaft against the panel hole: the footprint (from drawing R09N-003, `R0904N.pdf` p.2) puts the snap-in slots, and so the shaft, 7.0 mm from the pin row; the module CAD (`config/module.yaml` `pot.pins`, from the STEP) 6.7. The layout places the pins where the CAD does, so the shaft sits 0.3 mm above the CAD's hole centre, inside the hole's 0.5 mm radial play (`pot.hole_d`) | Reading both banked sources again; the first panel's test-fit (`pot.hole_d`'s own `decided_by`) |
| The pots' rotation sense (which end is clockwise). Checked 2026-09-30 against both banked drawings — `R0904N.pdf` p.2 and `RV09AF-40.pdf` p.3 draw pins 1-2-3 with the shaft at full CCW and say nothing about which end the wiper approaches, so the sheets' "CW toward pin 3" stays `[from memory]` | Goods-in, E10: turn each pot fully CCW and read pin 1 to 2 with an ohmmeter — near 0 Ω confirms the sheets; near the full track means swap `CW`/`CCW` on all three symbols before the legends are drawn |
| Whether the reasons for `J-B2B-MOD`'s allocation still hold once the board is laid out. The panel layout is settled (ADR 0024 points 11–13), and the reasons were re-read against it | The layout, against `mechanical/module/export/pcb-geometry.echo` |

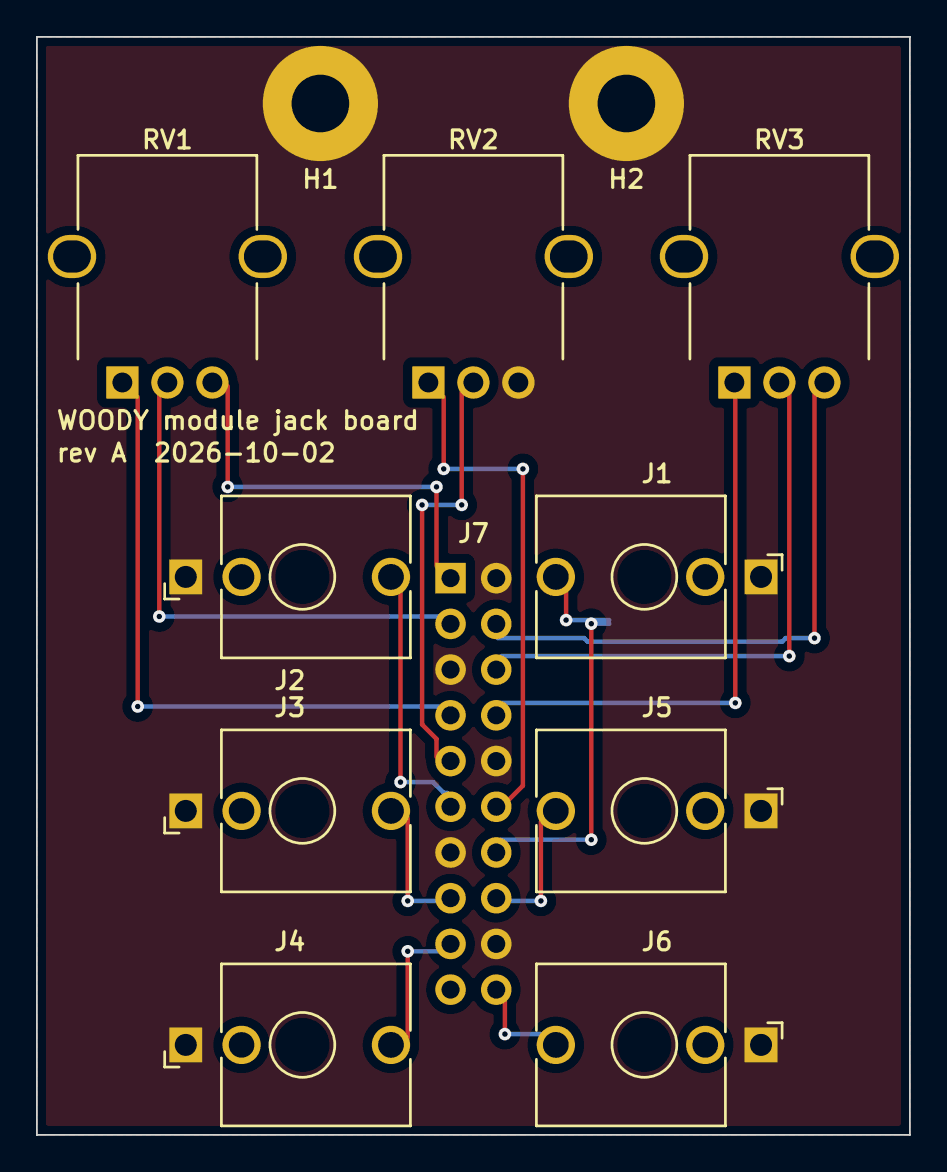
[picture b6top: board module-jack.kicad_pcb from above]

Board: 2 copper layers, 48.5 x 61.0 mm, 13 parts (1 on the bottom side), 15 nets.

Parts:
D2: PESD15VL1BA; D_SOD-323
H1, H2: M3 female-female hex spacer; MountingHole_3.2mm_M3_Pad
J1, J2, J3, J4, J5, J6: PJ398SM; Jack_3.5mm_QingPu_WQP-PJ398SM_Vertical_CircularHoles
J7: 2x10 2.54mm pin header; PinHeader_2x10_P2.54mm_Vertical
RV1, RV3: 50k linear; Potentiometer_SongHuei_R0904N_Single_Vertical
RV2: 10k linear; Potentiometer_SongHuei_R0904N_Single_Vertical

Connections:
/AGND_MOD: D2.2, H1.1, H2.1, J1.S, J2.S, J3.S, J4.S, J5.S, J6.S, J7.2, J7.5, J7.10, J7.13, J7.18, RV2.3
/BREATH_JACK: J2.T, J7.11
/BREATH_SHAPED: J7.1, RV1.3
/DAC_AVDD: J7.12, RV2.1
/GAIN_FLOOR: J7.7, RV1.1
/GAIN_WIPER: J7.3, RV1.2
/MOD1_JACK: J3.T, J7.15
/MOD2_JACK: J4.T, J7.17
/MOD3_JACK: J5.T, J7.16
/MOD4_JACK: J6.T, J7.20
/OFFSET_WIPER: J7.9, RV2.2
/PITCH_JACK: D2.1, J1.T, J7.14
/RESP_V_IN_HALF: J7.4, RV3.3
/RESP_V_SHAPED: J7.8, RV3.1
/RESP_WIPER: J7.6, RV3.2

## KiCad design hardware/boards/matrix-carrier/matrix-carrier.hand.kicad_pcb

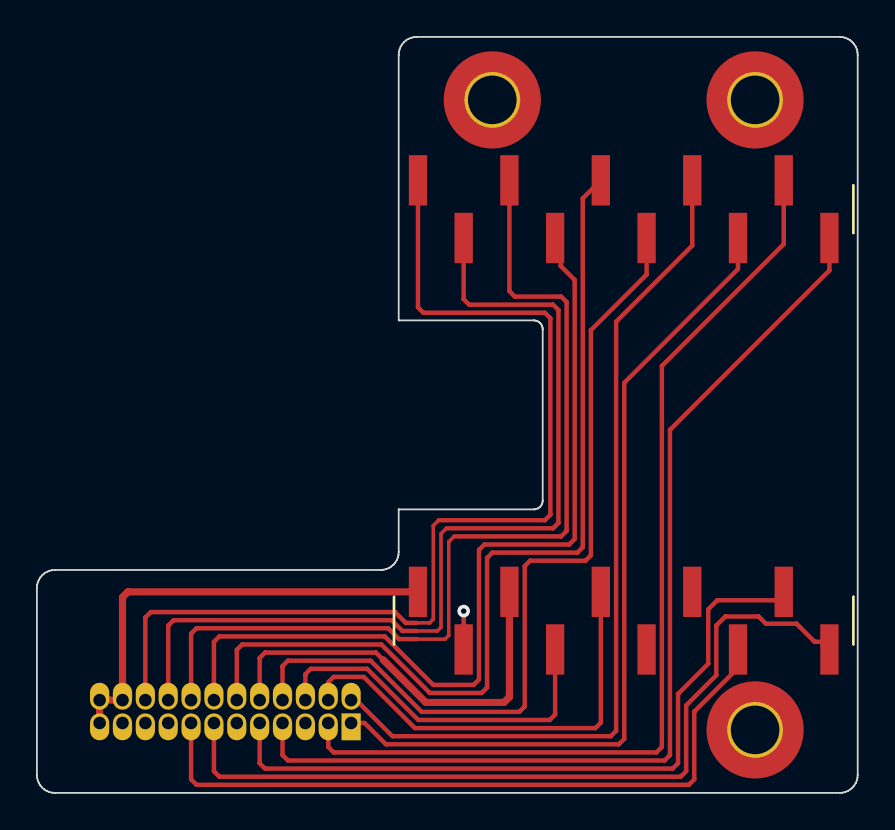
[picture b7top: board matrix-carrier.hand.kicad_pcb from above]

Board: 2 copper layers, 45.6 x 42.0 mm, 6 parts (1 on the bottom side), 18 nets.

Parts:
H1, H2, H3: mount hang; MountingHole_2.7mm_M2.5_Pad_TopBottom
J1: 2x12 1.27mm shrouded box header; IDC-Header_2x12_P1.27mm_XKB_X1270WR_Horizontal
J2, J3: 1x10 2.54mm pin header, SMD; PinHeader_1x10_P2.54mm_Vertical_SMD_Hanxia_PZ2.54-TP-YQ

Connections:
/DEV_3V3: J1.10, J2.3
/INST_5V_A: J1.22, J1.23, J1.24, J2.1
/IO1: J1.13, J2.10
/IO2: J1.9, J2.9
/IO3: J1.15, J2.8
/IO6: J1.4, J2.5
/IO7: J1.6, J2.4
/IO33: J1.20, J3.1
/IO34: J1.18, J3.2
/IO35: J1.16, J3.3
/IO36: J1.14, J3.4
/IO37: J1.12, J3.5
/IO38: J1.8, J3.6
/IO39: J1.2, J3.7
/IO40: J1.1, J3.8
/U0RXD: J1.7, J3.10
/U0TXD: J1.3, J3.9
PWR_GND: H1.1, H2.1, H3.1, J1.5, J1.11, J1.17, J1.21, J2.2

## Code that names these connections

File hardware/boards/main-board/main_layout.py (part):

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     then VS. The buffer stands under the sensor's near edge turned so RAW drops into its
     mouth-side column and VS leaves its tail-side column: the two run down under the
     sensor side by side with AGND between them. They used to cross there.
   - the reference buffer's feedback stands under and beside the pins it serves; REF_5V
     comes in along one line from the reference, tailward of the buffer, passing between
     R-ISO-REF's pads and R-FB-REF's so that it reaches its pin inside VS without a via.
   - the reference's input parts hang from REF_VIN's bus beyond the reference, the 12 V
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    "U1": (277.0, 16.85, ("1", "NE")),
    "R1": (280.3, SPI_Y, ("SCLK", "N")), "R2": (283.3, SPI_Y, ("MOSI", "N")), "R3": (286.3, SPI_Y, ("CS_MOD", "N")),
    "R40": (289.0, SPI_Y - 0.55, ("IO34", "S")),
    "R46": (284.913, 15.6, ("TXD_HDR", "W")),      # its header-side pad over J-UART pin 1
    # RXD's series resistor beside the header, its header pad toward pin 2 (pre-fab review S3)
    "R56": (289.1, 15.95, ("RXD_HDR", "W")),
    # the ADC branch's two series resistors (pre-fab review S1), on top over the long lanes a
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ADC_ROW = 17.5               # the ADC's row: divider, anti-alias, decoupling, bulk, supply resistor
REF_LINE = 20.5               # REF_5V's line from the reference to the buffer; the feedback parts stand on it
PLACE.update({
    # the buffer under the sensor's near edge, turned so SENSOR_RAW drops into pin 5 on the mouth
    # side and VS leaves on the tail side: the two no longer cross under the sensor
    "U3": (14.0, 25.5, ("5", "NW")),
    "C203": (8.9, 26.455, ("SENSOR_RAW", "N")), "C204": (8.9, 22.0, ("INST_POS12", "N")),
    # the reference buffer's feedback: C9 and R9 under the pins they serve, R7 and R8 in the
    # corridor VS climbs; REF_5V passes between R7's pads and between R8's to reach pin 3 inside VS
    "C9": (13.5, REF_LINE, ("REF_MINUS", "N")), "R9": (16.5, REF_LINE, ("BUF_OUT", "N")),
    "R7": (20.6, REF_LINE, ("VS", "N")), "R8": (19.55, 24.865, ("VS", "E")),
    # the reference, tailward on the same line: its output capacitors on the line, its input
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LED_CAP_DX = -6.5             # each LED's 100 nF: this far from its LED's centre, in the row, a millimetre between courtyards
KEEP_CAP = ("C38", "C26")     # the mouth-end LED's stands north of it, off the sensor; the first LED's is beyond the surge diode
PLACE["C11"] = (237.0, 12.5, ("BUCK_IN", "N"))   # its input pad level with the inductor and the regulator
PLACE["C43"] = (219.545, 18.5, ("BUCK_A_OUT", "E"))   # its output pad over the regulator's output pin
PLACE["C38"] = (26.85, 33.0, ("INST_POS12", "W"))

# Every part not named above keeps the place the reviewed board gave it.
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    A = "AGND_INST"
    # the sensor's output: down the mouth edge clear of the sensor's unused pads, through its
    # capacitor's pad, into the buffer's + input
    T("SENSOR_RAW", ["U10.4", (10.34, 45.9), (9.2, 44.76), (9.2, 27.405), "U3.5"])      # down into its capacitor's pad, and level out of it into the pin
    # the buffer's output: one trunk under its own body, pins 6 and 7 a stub each. North it
    # leaves between pins 5 and 4 for the breath pair's via; south between pins 8 and 1, round
    # the mouth side of the feedback capacitor, into the ADC's divider
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    T("ADC_VDD", ["R47.2", (42.888, 16.32), (42.518, 15.95), (30.0, 15.95)], PWR)
    T("ADC_VDD", [(37.47, 15.95), "C2.1"], PWR)
    T("ADC_VDD", [(32.03, 15.95), "C42.1"], PWR)
    T("ADC_VDD", ["C3.1", (30.0, 14.155)], PWR)       # the decoupler straight onto the supply pin, the bus teeing into it
    # 12 V for the buffer, its capacitor at the pin; and for the reference's input resistor
    T("INST_POS12", ["U3.8", (10.07, 23.595), (9.415, 24.25), (8.85, 24.25)], PWR)      # pin, via, capacitor: straight out of the pin, one step up, level into the via
    VIAS.append(("INST_POS12", 8.85, 24.25))
    T("INST_POS12", [(8.85, 24.25), (8.85, 22.95)], PWR)
    T("INST_POS12", ["R6.1", (48.25, 21.35), (47.5, 20.6)], PWR)      # straight out of the pad, one 45 into the via
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    the header on the bottom face to the LED driver. 3V3 is J-MCU pin 15 round the tail end (drawn in
    stage 3); its trunk starts by R49 and runs the bottom face toward the mouth."""
    # 12 V entry and the inrush switch
    T("UMBILICAL_POS12", ["J6.3", (294.64, 31.35), (276.35, 31.35)], 0.8)      # one 45 out of the pin, then one straight line into the surge diode's pad, north of the first LED   # to the surge diode, north of the first LED
    T("UMBILICAL_POS12", ["J6.3", (297.1, 32.31), (298.85, 30.56), "R41.1"], 0.6)   # level out of the pin, one 45, and straight down into R41's pad
    T("UMBILICAL_POS12", ["Q1.2", "C39.1", "R41.1"], 0.5)
    T("INRUSH_GATE", ["Q1.1", "C39.2", "R41.2", "R42.1"])
    T("INRUSH_GATE", ["Q1.1", "C40.1"])
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    T("BUCK_A_OUT", ["U5.3", "C43.1", "Q2.2"], 0.5)
    T("BUCK_A_OUT", [(229.8, 18.5), "C207.2"])
    T("BUCK_A_OUT", [(232.163, 18.5), "U13.3"])
    T("BUCK_A_OUT", ["U13.3", (233.125, 19.45), (233.3, 19.625), (233.3, 21.175), (233.475, 21.35), "U13.6"])      # between the pin rows: all the room there is for the two turns
    T("USBOR_GATE", ["U13.5", "Q2.1"])
    T("USBOR_VCAP", ["C207.1", "U13.1"])
    for pad, x, y in (("U13.2", 231.0, 20.4), ("C208.2", 241.35, 20.6), ("C43.2", 218.07, 16.9)):
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    # the module's SPI, from its resistors to J-UMB: SCLK comes down the tail side of the first LED
    T("SCLK", ["J6.4", (290.07, 29.77), (281.7, 21.4), (280.3, 21.4)])      # into its pad level, as near the centre as MOSI's pad lets the diagonal stand
    T("MOSI", ["J6.5", (288.3, 27.23), (283.3, 22.23), "R2.2"])
    T("CS_MOD", ["J6.7", (294.563, 21.113), "R3.2"])      # one 45 from the pin's centre, then level into the pad
    # the breath pair's last step to J-UMB
    T("BREATH_SENSE", ["J6.1", "R38.2"])
    T("BREATH_SENSE", [(293.25, 37.39), "D5.1"])
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    T("HOP_LT_RH", ["J5.6", (xh + RH, y6), (xh + RH - 0.9, y6 - 0.9), (xh + RH - 0.9, 35.0), (xh + RH - 0.9 - (35.0 - lt), lt), (82.2, lt)], FINE, "B")
    VIAS.append(("HOP_LT_RH", 82.2, lt))
    T("HOP_LT_RH", [(82.2, lt), (81.15, 32.0), (70.9, 32.0), (70.35, 31.45), (54.85, 31.45), (53.875, 32.425), "R44.2"])
    T("HOP_LT_QH", ["R44.1", (55.525, 33.975), (57.55, 36.0), (61.055, 36.0)])      # into pin 9, the end pin, across its long edge: the gap under the row has room for one line only


HOP_Y = 42.95                 # each hop's via, between its resistor's pad and the clamp's pad 5, and its line on the bottom face
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        T("CHAIN_SHLD", [f"{j}.4", (X(73.95), y4), (X(69.94), y4), f"{u}.1"])
        T("CHAIN_SHLD", [(X(73.95), y4), f"{tvs}.3"])
        # pins 6 and 10 of the header
        T("CHAIN_SER_LH" if lh else "HOP_LT_RH", [f"{tvs}.4", (X(73.95 + 0.1325), y6), f"{j}.6"])   # level with the pin's centre; the step is in the clamp's pad
        # (the left bead's 3V3 comes up from the mouth side, so its pad 2 faces the header; the right
        # bead's arrives along the far band from the tail, so its pad 2 is the far one and turns back
        # between the bead and the hop's resistor)
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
